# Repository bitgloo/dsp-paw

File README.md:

# dsp-paw

This is the DSP PAW "monorepo", containing the microcontroller firmware, add-on board design files, and the source code for the computer graphical interface (GUI).

*DSP PAW* (Digital Signal Processing Portable All-in-one Workstation) provides a solution for creating and studying DSP algorithms on embedded systems. Using the project's software and hardware with certain [NUCLEO development boards](https://www.st.com/en/evaluation-tools/stm32-nucleo-boards.html) will enable you to portably design DSP algorithms, without the need for external tools or laboratory equipment.

## Project components

1. [Firmware](https://code.bitgloo.com/bitgloo/dsp-paw/src/branch/main/firmware) that allows users to load and execute custom DSP algorithms for real-time signal processing.
2. [A custom add-on board](https://code.bitgloo.com/bitgloo/dsp-paw/src/branch/main/hardware) which provides the necessary circuitry for interfacing with external signals and the host computer.
3. [Computer software](https://code.bitgloo.com/bitgloo/dsp-paw/src/branch/main/gui) that facilitates algorithm design, execution, and detailed analysis.

## Features

* Real-time signal processing: signal read by the ADC are streamed through the loaded algorithm and output via the DAC.
* The core firmware facilitates algorithm uploads over USB, enabling a fast design and test process.
* Supports signal sampling rates from 8kS/s up to 96kS/s, with buffer size of up to 4,096 samples.
* Supports external signals between -2V and +2V.
* Two potentiometers for adjusting algorithm parameters while the algorithm is running.
* An on-board signal generator that eliminates the need for input signals from external hardware.
* Numerous analysis features, including signal visualization and algorithm execution time measurement, eliminate the need for other test equipment like oscilloscopes.

## Build notes

The add-on board was designed using [KiCad](https://www.kicad.org/).

Both the firmware and user interface software are written in C++, and have single Makefiles for their build processes. Both also depend on git submodules, so be sure to fetch those before compilation.

The firmware additionally requires the `arm-none-eabi` toolchain, and the GUI requires [SDL 2.0](https://www.libsdl.org/).

## Learn more

The [project's wiki](https://code.bitgloo.com/bitgloo/dsp-paw/wiki) will be updated over time with more information about all aspects of the project.

### Licensing

DSP PAW source code is licensed under version three of the GNU General Public License. The add-on board design files are licensed under the CERN Open Hardware License Version 2 - Strongly Reciprocal. See the `LICENSE` files in each component's folder for more information.

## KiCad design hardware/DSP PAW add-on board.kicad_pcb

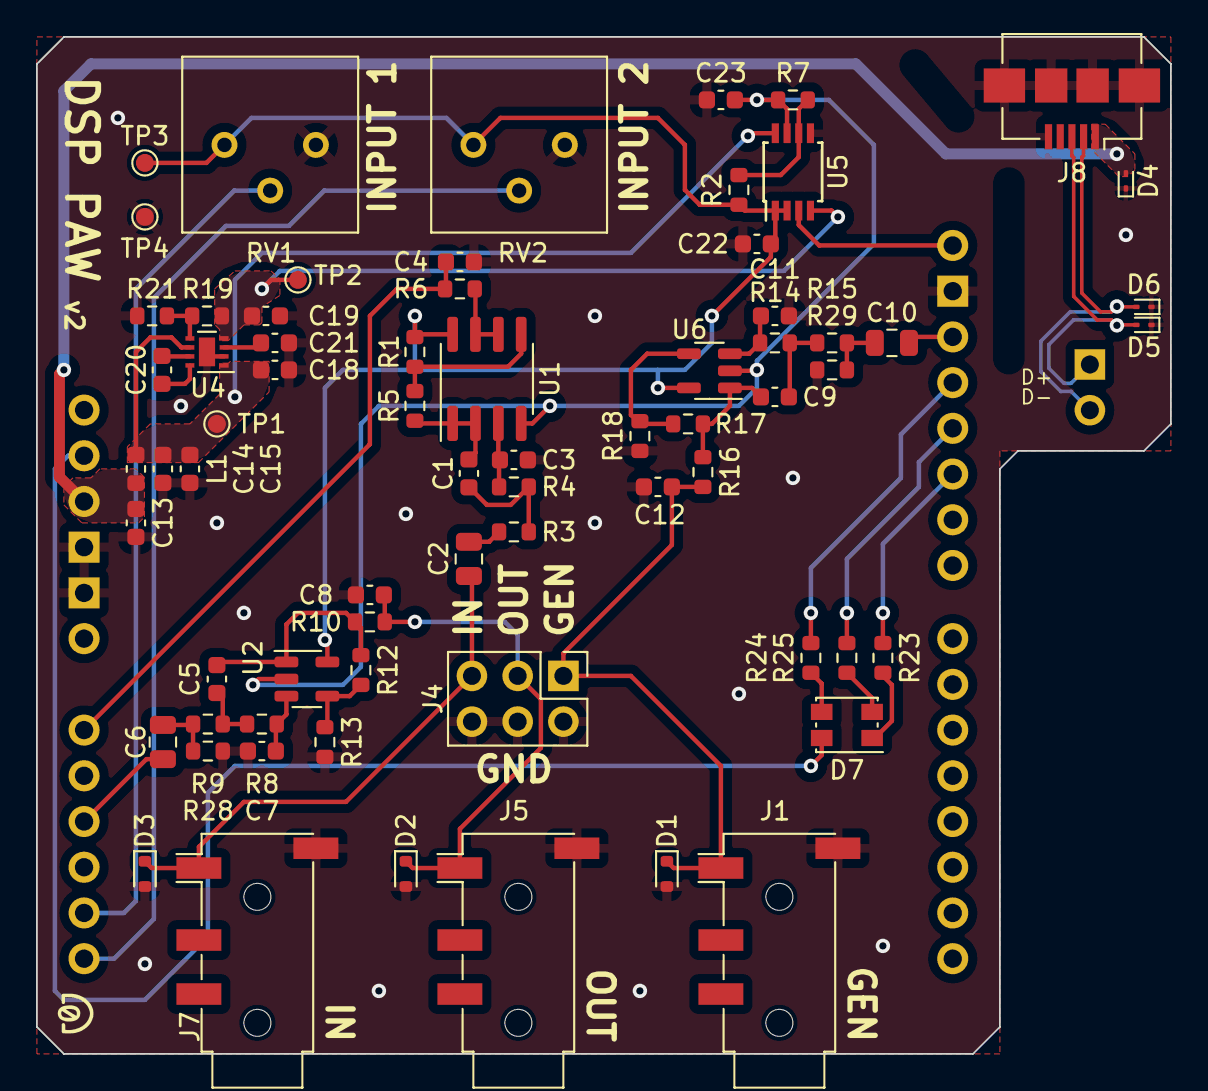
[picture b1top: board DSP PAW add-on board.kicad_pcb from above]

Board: 2 copper layers, 63.0 x 56.5 mm, 71 parts (1 on the bottom side), 45 nets.

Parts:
A2: Arduino_Uno_R1_Shield; Arduino_Uno_R2_Shield
C1: 140p; C_0603_1608Metric
C2, C6, C10: 10u; C_0805_2012Metric
C3, C7, C11: 100p; C_0603_1608Metric
C4, C13: 10n; C_0603_1608Metric
C5, C9: 105p; C_0603_1608Metric
C8, C12: DNP; C_0603_1608Metric
C14: 100n; C_0603_1608Metric
C15, C18, C21: 4.7u; C_0603_1608Metric
C19: 2.2u; C_0603_1608Metric
C20, C22, C23: 1u; C_0603_1608Metric
D1, D2, D3: ESD5Z2.5T1G; D_SOD-523
D4, D5, D6: DF2B7AFS,L3M; D_SOD-923
D7: LED_RAGB; LED_Kingbright_AAA3528ESGCT
J1, J5, J7: AudioJack2_Ground; Jack_3.5mm_PJ320D_Horizontal
J3: Conn_01x02; PinHeader_1x02_P2.54mm_Vertical
J4: Conn_02x03_Odd_Even; PinHeader_2x03_P2.54mm_Vertical
J8: USB_B_Micro; USB_Micro-B_Amphenol_10104110_Horizontal
L1: 33@100MHz; L_0603_1608Metric
R1, R2, R5, R7: 10k/0.1%; R_0603_1608Metric
R3: 8.45k/1%; R_0603_1608Metric
R4: 13.3k/1%; R_0603_1608Metric
R6: 200; R_0603_1608Metric
R8, R14: 22.1k/0.5%; R_0603_1608Metric
R9, R15: 6.81k/0.5%; R_0603_1608Metric
R10, R16: 0; R_0603_1608Metric
R12, R13, R17, R18: 2.49k/0.5%; R_0603_1608Metric
R19: 174k/1%; R_0603_1608Metric
R21: 56k/1%; R_0603_1608Metric
R23: 560; R_0603_1608Metric
R24, R25: 240; R_0603_1608Metric
R28, R29: 100k; R_0603_1608Metric
RV1, RV2: 10K; Potentiometer_Bourns_3386P_Vertical
TP1, TP2, TP3, TP4: TestPoint; TestPoint_Pad_D1.0mm
U1: TLV9162; SOIC-8_3.9x4.9mm_P1.27mm
U2, U6: OPA1677; SOT-23-5
U4: LM27761; WSON-8-1EP_2x2mm_P0.5mm_EP0.9x1.6mm
U5: OPA2310; TSSOP-8_3x3mm_P0.65mm

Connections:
+3V3: C22.1, R1.2, R2.2, RV1.1, RV2.1, TP3.1, U1.8 (V+), U2.5 (V+), U5.1, U5.2 (-), U6.5 (V+)
+5V: C14.1, C15.1, C18.1, L1.2, TP1.1, U4.1 (VIN), U4.6 (EN), U5.8 (V+)
-3V3: C23.1, R7.2, U1.4 (V-), U2.2 (V-), U5.7, U6.2 (V-)
-5V: C19.1, R19.1, TP2.1, U4.4 (VOUT), U5.4 (V-)
GENERATOR: C12.2, D1.1 (K), J1.T, J4.1, R16.1
GENERATOR_MCU: A2.D13, C10.2
GND: A2.GND1 (GND), A2.GND2 (GND), A2.GND3 (GND), C3.2, C4.2, C7.2, C8.1, C11.2, C12.1, C13.2, C14.2, C15.2, C18.2, C19.2, C21.2, C22.2, C23.2, D1.2 (A), D2.2 (A), D3.2 (A), D4.1 (A1), D5.1 (A1), D6.1 (A1), J1.S, J4.2, J4.4, J4.6, J5.S, J7.S, J8.5 (GND), J8.6 (Shield), R13.2, R18.2, R21.2, R28.1, R29.1, RV1.3, RV2.3, TP4.1, U4.2 (GND), U4.9 (PAD), U5.5 (+)
LED_B: A2.D10 (D10_CS), R23.1
LED_G: A2.D11, R25.1
LED_R: A2.D12, R24.1
unnamed: C1.1, R3.2, R4.1
unnamed: C2.2, R3.1
unnamed: C5.1, R10.2, R12.1, U2.1
unnamed: C5.2, R8.2, R9.1
unnamed: C6.1, R9.2, R28.2
unnamed: C9.1, R16.2, R17.1, U6.1
unnamed: C9.2, R14.2, R15.1
unnamed: C10.1, R15.2, R29.2
unnamed: D7.1 (BK), R23.2
unnamed: D7.4 (GK), R25.2
unnamed: D7.3 (RK), R24.2
unnamed: C3.1, R4.2, U1.3 (+)
unnamed: C1.2, R5.1, U1.1, U1.2 (-)
unnamed: R1.1, R5.2, U1.5 (+)
unnamed: R6.1, U1.6 (-), U1.7
unnamed: C7.1, R8.1, U2.3 (+)
unnamed: R12.2, R13.1, U2.4 (-)
unnamed: C20.1, U4.8 (C+)
unnamed: C20.2, U4.7 (C-)
unnamed: C21.1, U4.3 (CPOUT)
unnamed: R19.2, R21.1, U4.5 (VFB)
unnamed: R2.1, R7.1, U5.6 (-)
unnamed: C11.1, R14.1, U6.3 (+)
unnamed: R17.2, R18.1, U6.4 (-)
PC0/POT1: A2.A4 (A4/SDA), RV1.2
PC1/POT2: A2.A5 (A5/SCL), RV2.2
SIGNAL_IN: C2.1, D3.1 (K), J4.5, J7.T
SIGNAL_IN_MCU: A2.A0, C4.1, R6.2
SIGNAL_OUT: C8.2, D2.1 (K), J4.3, J5.T, R10.1
SIGNAL_OUT_MCU: A2.A2, C6.2
USB_D_N: D6.2 (A2), J3.2, J8.2 (D-)
USB_D_P: D5.2 (A2), J3.1, J8.3 (D+)
VBUS: A2.5V1 (5V), C13.1, D4.2 (A2), J8.1 (VBUS), L1.1
VCC: A2.3V3 (3.3V), D7.2 (A)
VDDA: A2.AREF, U5.3 (+)

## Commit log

2023-08-09 initial commit
    * combine all source files into this monorepo
    * convert all third-party source packages into submodules
    * small fixes due to changes in latest third-part packages
2023-08-17 finalize pcb design; add layout file
2023-08-19 pcb design finalization
2023-08-20 design finalized; publish pdfs
2023-09-05 fix blank IDs for imgui controls
2023-09-05 update pins for LEDs and knobs
2023-09-05 add attenuation example
2023-09-05 wip: schematic fixes based on testing
2023-09-12 vdda buffer; vdda for pots; other fixes
2023-09-23 add frequency plot
2023-09-23 add hardware specification doc
2023-09-23 use nucleo 3.3v vdda; add 2nd low-pass stage to input
2023-09-23 finalize rev2 schematic
2023-09-28 gui: don't show whitespace
2023-10-08 remove unintentionally committed files
2023-10-08 finish rev2 layout
2023-10-08 add guidebook
2023-10-08 add to firmware documentation
2023-10-09 add 3d models back; flip USB data header
2023-10-10 small fixes; add compile checks

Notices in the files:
hardware/DSP PAW add-on board.kicad_pcb:
Released under the CERN Open Hardware Licence Version 2 - Strongly Reciprocal
